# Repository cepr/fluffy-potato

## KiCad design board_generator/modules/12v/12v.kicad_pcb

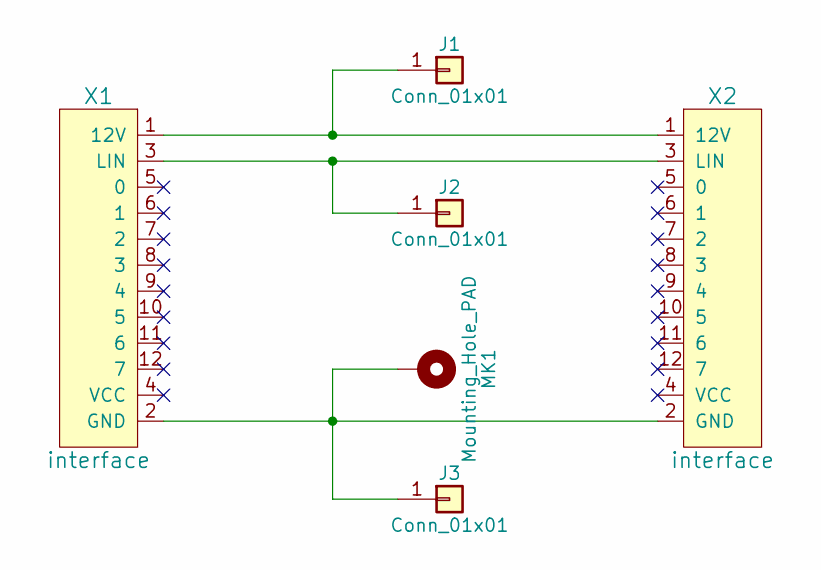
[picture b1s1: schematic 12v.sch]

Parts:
J1, J2, J3: Conn_01x01; SolderWirePad_single_SMD_5x10mm
MK1: Mounting_Hole_PAD; MountingHole_3.2mm_M3_Pad
X1, X2: interface

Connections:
unnamed: J1.1, X1.1 (12V), X2.1 (12V)
unnamed: J2.1, X1.3 (LIN), X2.3 (LIN)
unnamed: J3.1, MK1.1, X1.2 (GND), X2.2 (GND)

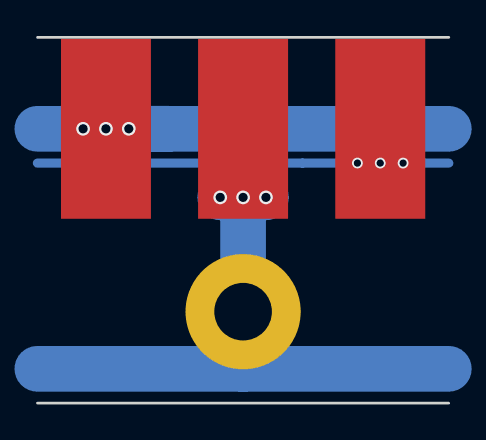
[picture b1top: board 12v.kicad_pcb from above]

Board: 2 copper layers, 22.9 x 20.3 mm, 6 parts (0 on the bottom side), 3 nets.

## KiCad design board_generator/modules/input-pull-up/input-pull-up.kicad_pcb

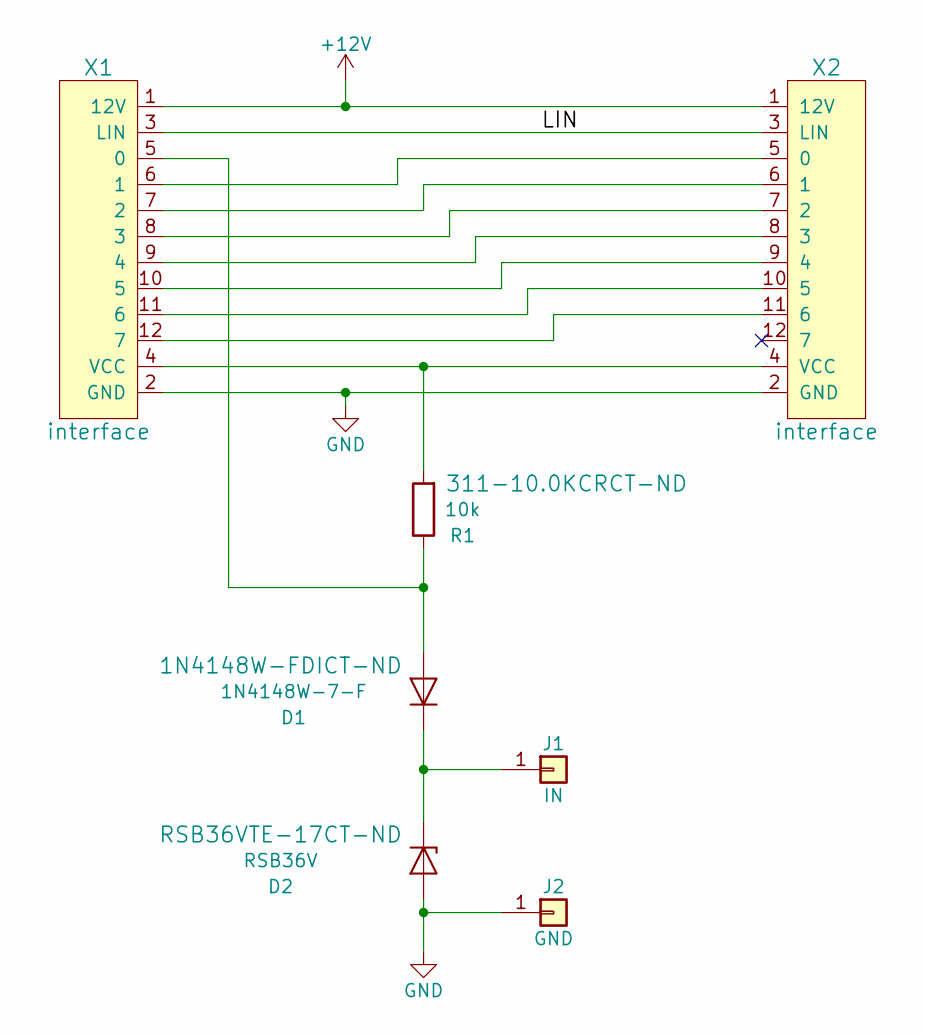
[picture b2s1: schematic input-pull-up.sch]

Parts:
D1: 1N4148W-7-F; D_SOD-123; DIGIKEY 1N4148W-FDICT-ND
D2: RSB36V; D_SOD-323; DIGIKEY RSB36VTE-17CT-ND
J1: IN; SolderWirePad_single_SMD_15x40mil
J2: GND; SolderWirePad_single_SMD_15x40mil
R1: 10k; R_0805; DIGIKEY 311-10.0KCRCT-ND
X1, X2: interface

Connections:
+12V: X1.1 (12V), X2.1 (12V)
/LIN: X1.3 (LIN), X2.3 (LIN)
GND: D2.2 (A), J2.1, X1.2 (GND), X2.2 (GND)
unnamed: D1.1 (K), D2.1 (K), J1.1
unnamed: D1.2 (A), R1.1, X1.5 (0)
unnamed: R1.2, X1.4 (VCC), X2.4 (VCC)
unnamed: X1.6 (1), X2.5 (0)
unnamed: X1.7 (2), X2.6 (1)
unnamed: X1.8 (3), X2.7 (2)
unnamed: X1.9 (4), X2.8 (3)
unnamed: X1.10 (5), X2.9 (4)
unnamed: X1.11 (6), X2.10 (5)
unnamed: X1.12 (7), X2.11 (6)

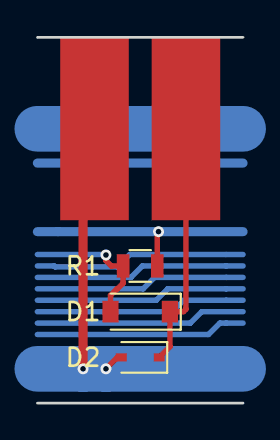
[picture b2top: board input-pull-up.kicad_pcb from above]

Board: 2 copper layers, 11.4 x 20.3 mm, 7 parts (0 on the bottom side), 13 nets.

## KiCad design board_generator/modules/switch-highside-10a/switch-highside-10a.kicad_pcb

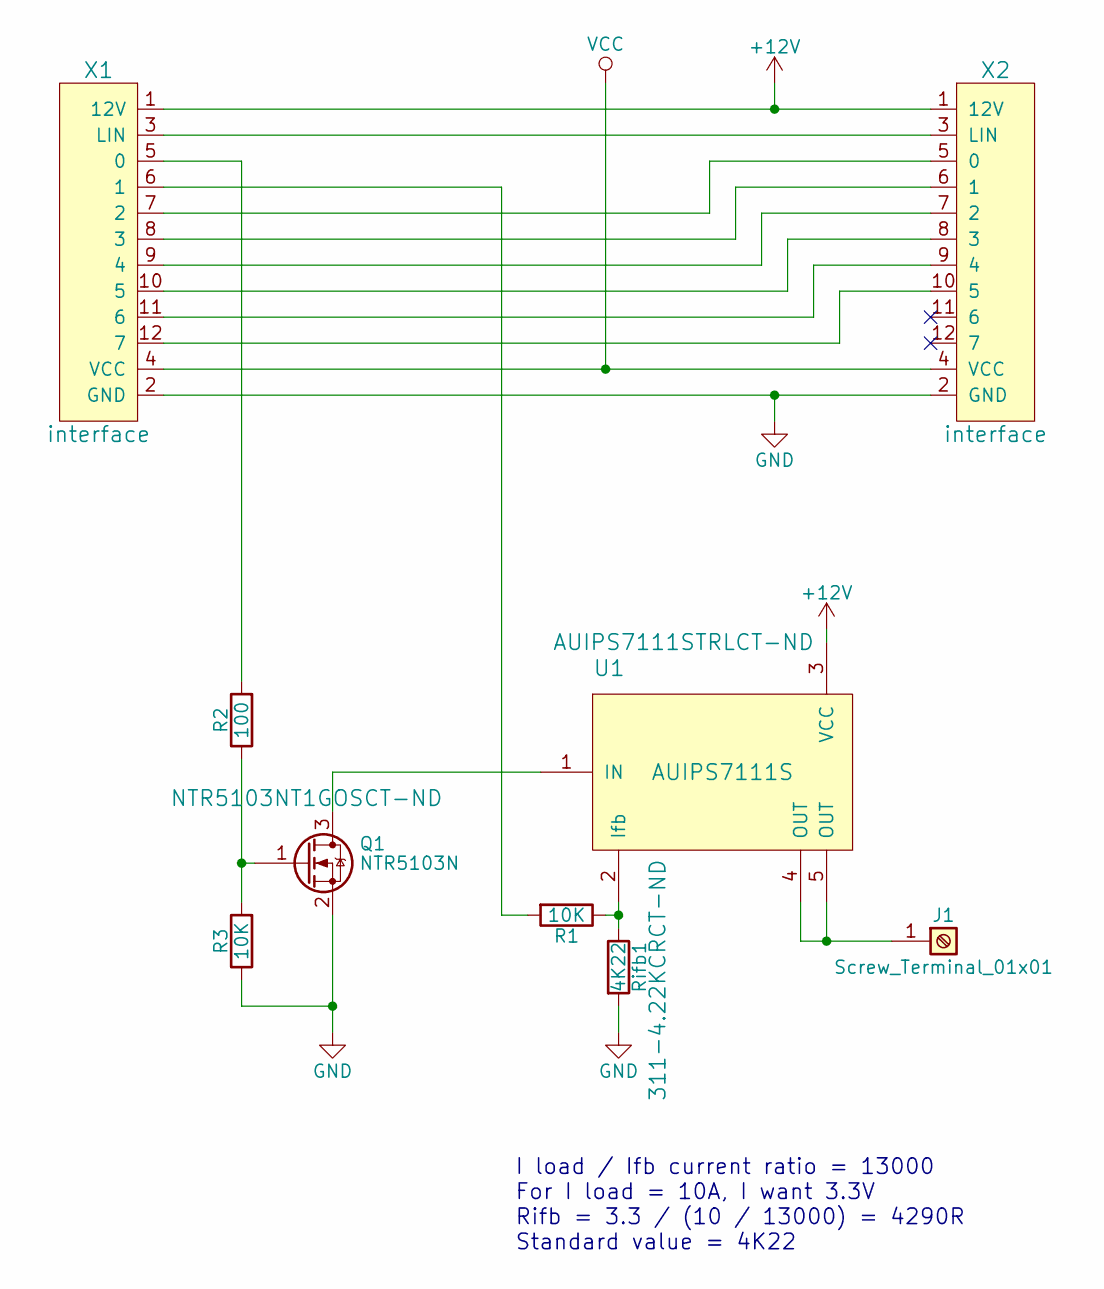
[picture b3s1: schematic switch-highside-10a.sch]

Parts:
J1: Screw_Terminal_01x01; TERM_SCREW_M3
Q1: NTR5103N; SOT-23; DIGIKEY NTR5103NT1GOSCT-ND
R1, R3: 10K; R_0805_HandSoldering; DIGIKEY 311-10.0KCRCT-ND
R2: 100; R_0805_HandSoldering; DIGIKEY 311-100CRCT-ND
Rifb1: 4K22; R_0805_HandSoldering; DIGIKEY 311-4.22KCRCT-ND
U1: AUIPS7111S; TO-263-5_TabPin3; DIGIKEY AUIPS7111STRLCT-ND
X1, X2: interface

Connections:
+12V: U1.3 (VCC), X1.1 (12V), X2.1 (12V)
GND: Q1.2 (S), R3.1, Rifb1.2, X1.2 (GND), X2.2 (GND)
unnamed: J1.1, U1.4 (OUT), U1.5 (OUT)
unnamed: Q1.1 (G), R2.1, R3.2
unnamed: Q1.3 (D), U1.1 (IN)
unnamed: R1.1, Rifb1.1, U1.2 (Ifb)
unnamed: R1.2, X1.6 (1)
unnamed: R2.2, X1.5 (0)
unnamed: X1.3 (LIN), X2.3 (LIN)
unnamed: X1.7 (2), X2.5 (0)
unnamed: X1.8 (3), X2.6 (1)
unnamed: X1.9 (4), X2.7 (2)
unnamed: X1.10 (5), X2.8 (3)
unnamed: X1.11 (6), X2.9 (4)
unnamed: X1.12 (7), X2.10 (5)
VCC: X1.4 (VCC), X2.4 (VCC)

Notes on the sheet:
I load / Ifb current ratio = 13000 For I load = 10A, I want 3.3V Rifb = 3.3 / (10 / 13000) = 4290R Standard value = 4K22

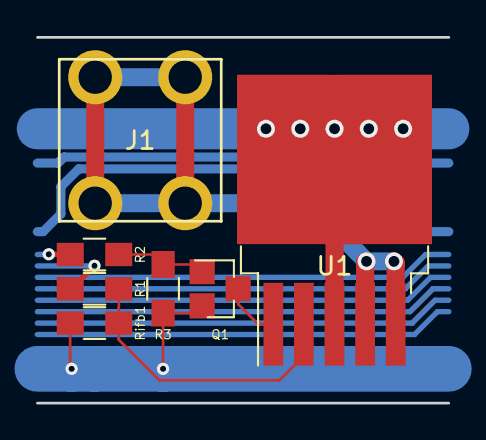
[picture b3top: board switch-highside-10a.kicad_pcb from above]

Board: 2 copper layers, 22.9 x 20.3 mm, 9 parts (0 on the bottom side), 16 nets.

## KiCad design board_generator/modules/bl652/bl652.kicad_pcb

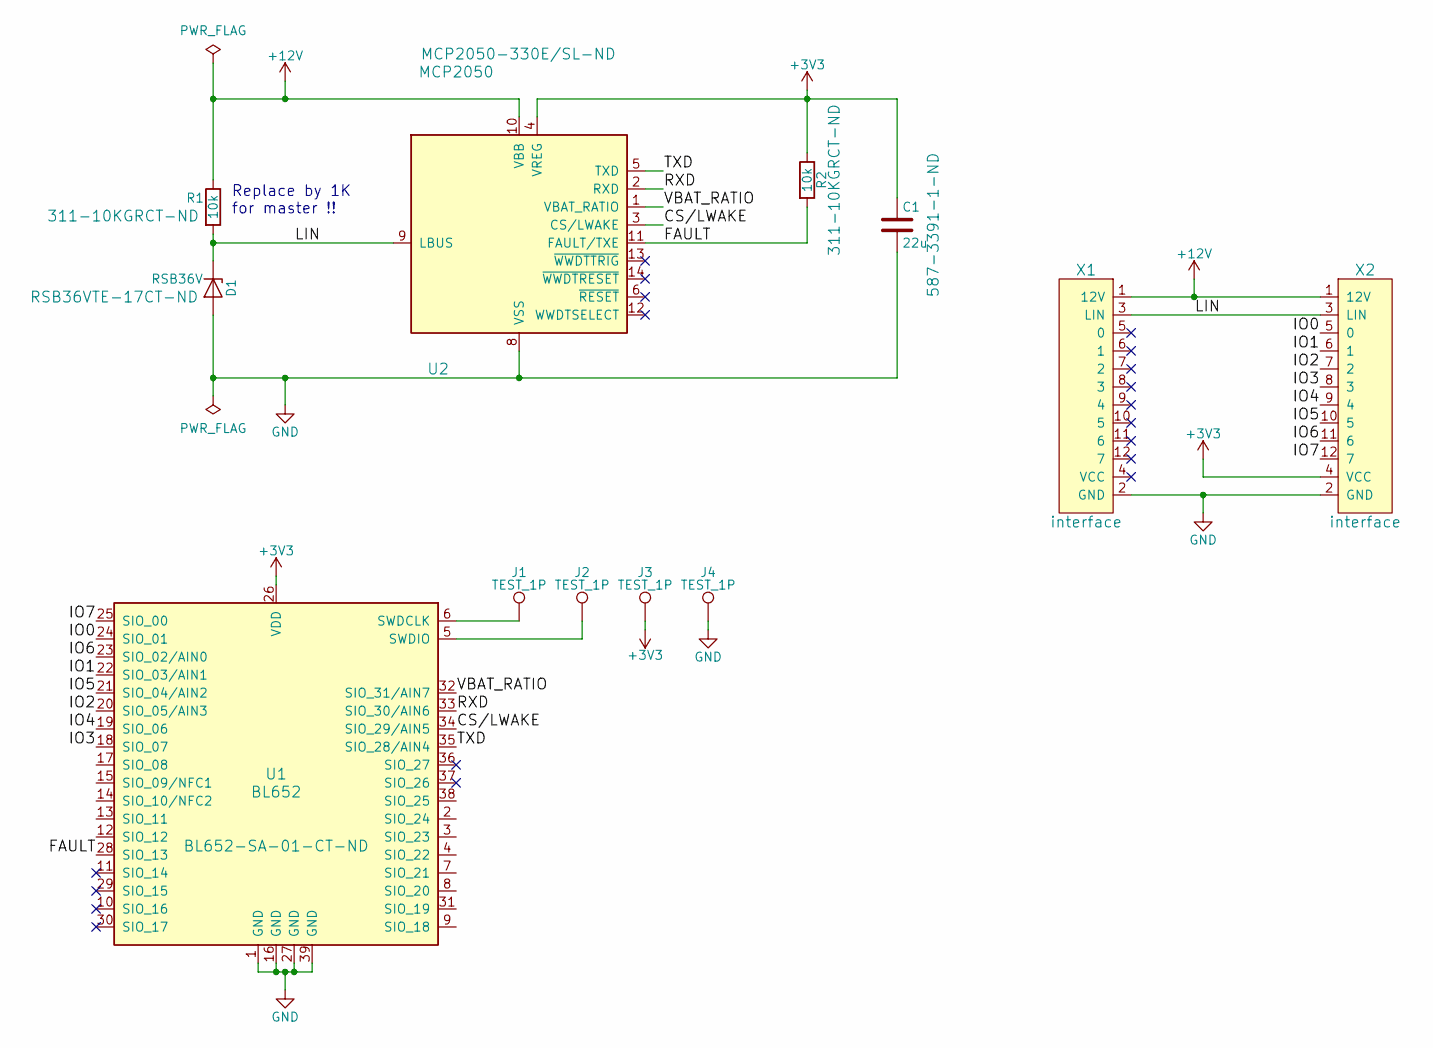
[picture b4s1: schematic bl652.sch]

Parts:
C1: 22u; C_0805_HandSoldering; DIGIKEY 587-3391-1-ND
D1: RSB36V; D_SOD-323_HandSoldering; DIGIKEY RSB36VTE-17CT-ND
J1, J2, J3, J4: TEST_1P; Measurement_Point_Square-SMD-Pad_Small
R1, R2: 10k; R_0603_HandSoldering; DIGIKEY 311-10KGRCT-ND
U1: BL652; Laird_BL652; DIGIKEY BL652-SA-01-CT-ND
U2: MCP2050; SOIC-14_3.9x8.7mm_Pitch1.27mm; DIGIKEY MCP2050-330E/SL-ND
X1, X2: interface

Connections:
+3V3: C1.1, J3.1, R2.1, U1.26 (VDD), U2.4 (VREG), X2.4 (VCC)
+12V: R1.1, U2.10 (VBB), X1.1 (12V), X2.1 (12V)
/CS/LWAKE: U1.34 (SIO_29/AIN5), U2.3 (CS/LWAKE)
/FAULT: R2.2, U1.28 (SIO_13), U2.11 (FAULT/TXE)
/IO0: U1.24 (SIO_01), X2.5 (0)
/IO1: U1.22 (SIO_03/AIN1), X2.6 (1)
/IO2: U1.20 (SIO_05/AIN3), X2.7 (2)
/IO3: U1.18 (SIO_07), X2.8 (3)
/IO4: U1.19 (SIO_06), X2.9 (4)
/IO5: U1.21 (SIO_04/AIN2), X2.10 (5)
/IO6: U1.23 (SIO_02/AIN0), X2.11 (6)
/IO7: U1.25 (SIO_00), X2.12 (7)
/LIN: D1.1 (K), R1.2, U2.9 (LBUS), X1.3 (LIN), X2.3 (LIN)
/RXD: U1.33 (SIO_30/AIN6), U2.2 (RXD)
/TXD: U1.35 (SIO_28/AIN4), U2.5 (TXD)
/VBAT_RATIO: U1.32 (SIO_31/AIN7), U2.1 (VBAT_RATIO)
GND: C1.2, D1.2 (A), J4.1, U1.1 (GND), U1.16 (GND), U1.27 (GND), U1.39 (GND), U2.8 (VSS), X1.2 (GND), X2.2 (GND)
unnamed: J1.1, U1.6 (SWDCLK)
unnamed: J2.1, U1.5 (SWDIO)

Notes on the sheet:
Replace by 1K for master !!

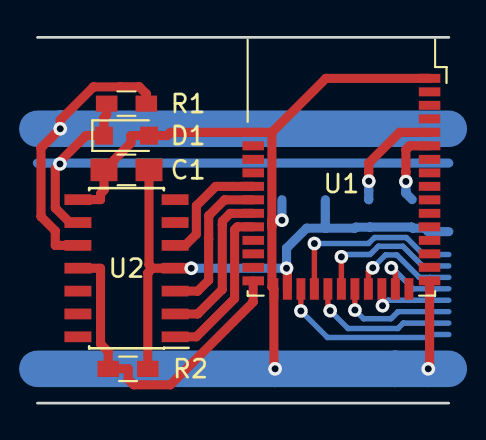
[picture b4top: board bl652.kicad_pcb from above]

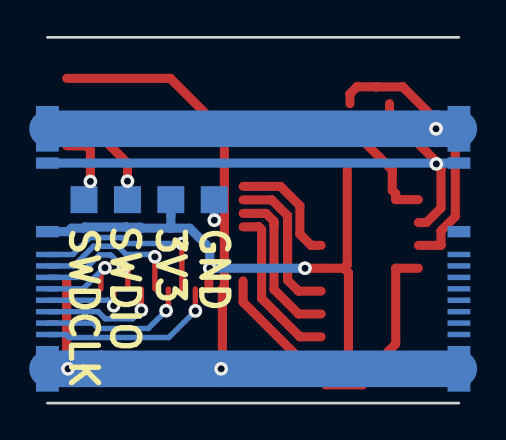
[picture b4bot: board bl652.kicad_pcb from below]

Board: 2 copper layers, 22.9 x 20.3 mm, 12 parts (4 on the bottom side), 19 nets.

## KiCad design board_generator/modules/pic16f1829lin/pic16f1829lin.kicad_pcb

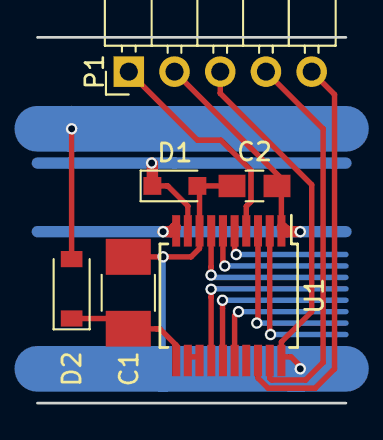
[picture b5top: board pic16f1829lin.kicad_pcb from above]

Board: 2 copper layers, 17.1 x 20.3 mm, 8 parts (0 on the bottom side), 17 nets.

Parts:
C1: 10uF; C_1210_HandSoldering
C2: 1uF; C_0805_HandSoldering
D1: RSB36V; D_SOD-323_HandSoldering
D2: 1N4148W-7-F; D_SOD-123
P1: MOLEX-22-28-6050; Pin_Header_Angled_1x05_Pitch2.54mm
U1: PIC16F1829LIN; SSOP-20_5.3x7.2mm_Pitch0.65mm
X1, X2: interface

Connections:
+5V: C2.1, P1.2, U1.1, U1.10, X1.4, X2.4
+12V: D2.2, X1.1, X2.1
//MCLR: P1.1, U1.4
/ICSPCLK: P1.5, U1.18
/ICSPDAT: P1.4, U1.19
/LBUS: D1.1, U1.9, X1.3, X2.3
/RA4: U1.3, X2.11
/RA5: U1.2, X2.12
/RC0: U1.16, X2.10
/RC1: U1.15, X2.9
/RC2: U1.14, X2.8
/RC3: U1.7, X2.7
/RC4: U1.6, X2.6
/RC5: U1.5, X2.5
GND: C1.2, C2.2, D1.2, P1.3, U1.8, U1.20, X1.2, X2.2
unnamed: C1.1, D2.1, U1.11
unnamed: U1.12, U1.13

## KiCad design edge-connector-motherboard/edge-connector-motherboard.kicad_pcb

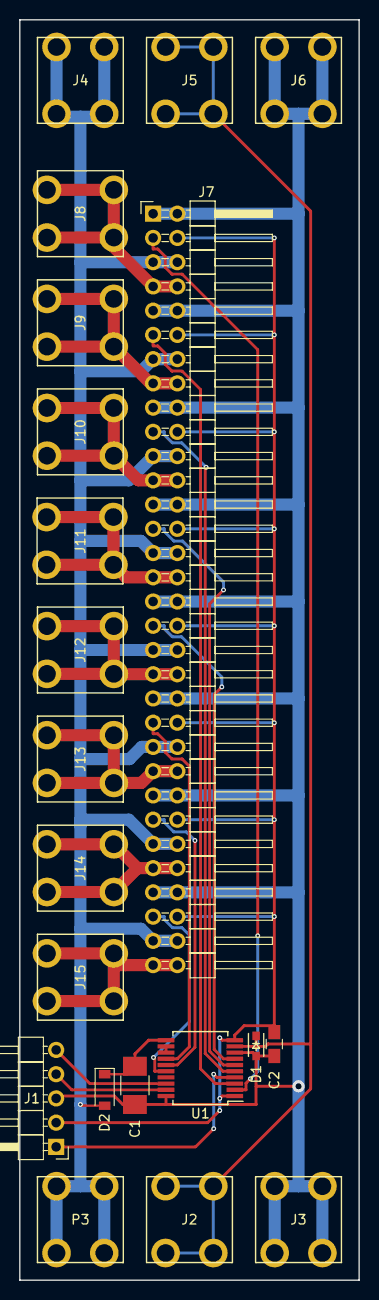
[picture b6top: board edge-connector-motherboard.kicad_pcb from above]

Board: 2 copper layers, 35.6 x 132.1 mm, 21 parts (0 on the bottom side), 26 nets.

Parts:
C1: 10uF; C_1210_HandSoldering
C2: 1uF; C_0805_HandSoldering
D1: RSB36V; SOD-323_HandSoldering
D2: 1N4148W-7-F; D_SOD-123
J1, J2, J3, J4, J5, J6, J8, J9, J10, J11, J12, J13, J14, J15: Screw_Terminal_1x01; TERM_SCREW_M3
J7: CONN_02X32; Pin_Header_Angled_2x32_Pitch2.54mm
P3: MOLEX-22-28-6050; Pin_Header_Angled_1x05_Pitch2.54mm
U1: PIC16F1829LIN; SSOP-20_5.3x7.2mm_Pitch0.65mm

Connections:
+5V: C2.1, J7.4, J7.12, J7.20, J7.28, J7.36, J7.44, J7.52, J7.60, P3.2, U1.1, U1.10
+12V: D2.2, J1.1, J4.1, J7.5, J7.6, J7.13, J7.14, J7.21, J7.22, J7.29, J7.30, J7.37, J7.38, J7.45, J7.46, J7.53, J7.54, J7.61, J7.62
/D1: J7.3, U1.2
/D2: J7.11, U1.3
/D3: J7.19, U1.5
/D4: J7.27, U1.6
/D5: J7.35, U1.7
/D6: J7.43, U1.14
/D7: J7.51, U1.15
/D8: J7.59, U1.16
/E1: J7.7, J7.8, J8.1
/E2: J7.15, J7.16, J9.1
/E3: J7.23, J7.24, J10.1
/E4: J7.31, J7.32, J11.1
/E5: J7.39, J7.40, J12.1
/E6: J7.47, J7.48, J13.1
/E7: J7.55, J7.56, J14.1
/E8: J7.63, J7.64, J15.1
/PIC16F1829LIN//MCLR: P3.1, U1.4
/PIC16F1829LIN/ICSPCLK: P3.5, U1.18
/PIC16F1829LIN/ICSPDAT: P3.4, U1.19
/PIC16F1829LIN/LBUS: D1.1, J2.1, J5.1, U1.9
GND: C1.2, C2.2, D1.2, P3.3, U1.8, U1.20
GNDPWR: J3.1, J6.1, J7.1, J7.2, J7.9, J7.10, J7.17, J7.18, J7.25, J7.26, J7.33, J7.34, J7.41, J7.42, J7.49, J7.50, J7.57, J7.58
unnamed: C1.1, D2.1, U1.11
unnamed: U1.12, U1.13

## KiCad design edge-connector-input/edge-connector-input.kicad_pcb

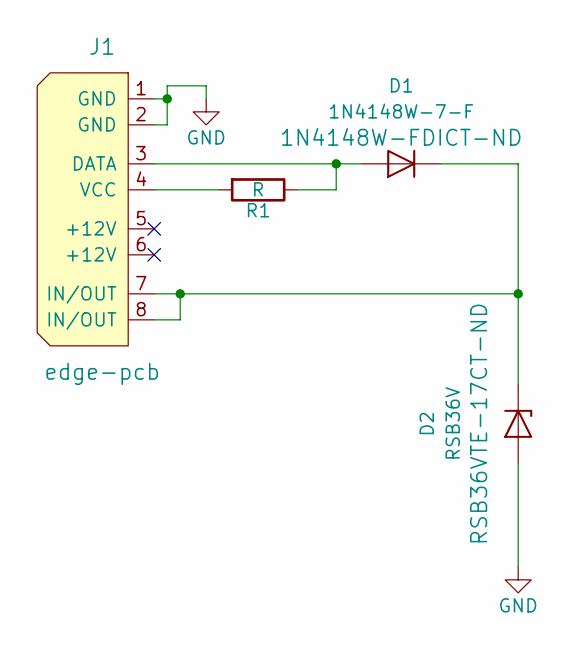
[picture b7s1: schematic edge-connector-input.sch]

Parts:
D1: 1N4148W-7-F; D_SOD-123; DIGIKEY 1N4148W-FDICT-ND
D2: RSB36V; D_SOD-323; DIGIKEY RSB36VTE-17CT-ND
J1: edge-pcb
R1: R; R_0805

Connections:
GND: D2.2 (A), J1.1 (GND), J1.2 (GND)
unnamed: D1.1 (K), D2.1 (K), J1.7 (IN/OUT), J1.8 (IN/OUT)
unnamed: D1.2 (A), J1.3 (DATA), R1.1
unnamed: J1.4 (VCC), R1.2

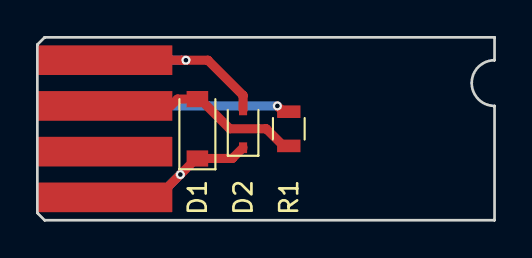
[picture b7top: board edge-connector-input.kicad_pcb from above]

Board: 2 copper layers, 25.4 x 10.2 mm, 4 parts (0 on the bottom side), 4 nets.

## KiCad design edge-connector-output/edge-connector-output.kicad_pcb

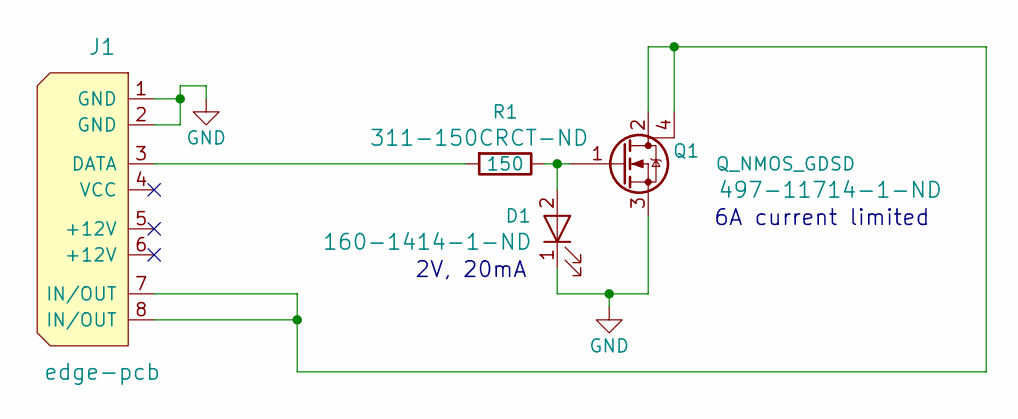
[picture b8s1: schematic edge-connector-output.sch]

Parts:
D1: LITEON-LTST-C170KGKT; LED_0805; DIGIKEY 160-1414-1-ND
J1: edge-pcb
Q1: Q_NMOS_GDSD; SOT-223; DIGIKEY 497-11714-1-ND
R1: 150; R_0805; DIGIKEY 311-150CRCT-ND

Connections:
GND: D1.1 (K), J1.1 (GND), J1.2 (GND), Q1.3 (S)
unnamed: D1.2 (A), Q1.1 (G), R1.1
unnamed: J1.3 (DATA), R1.2
unnamed: J1.7 (IN/OUT), J1.8 (IN/OUT), Q1.2 (D), Q1.4 (D)

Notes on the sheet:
2V, 20mA
6A current limited

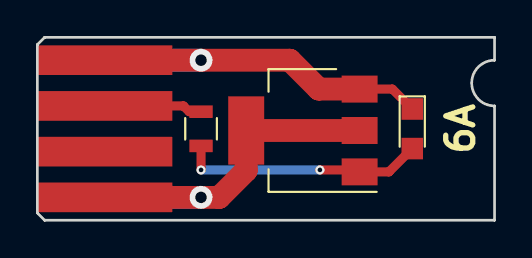
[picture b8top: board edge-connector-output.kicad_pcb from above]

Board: 2 copper layers, 25.4 x 10.2 mm, 4 parts (0 on the bottom side), 4 nets.

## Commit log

2016-10-03 First working firmware
2016-10-12 4x13A switch - rev 1
2016-10-12 9 inputs LIN module - rev1
2016-10-16 Activating sleep mode - down to 180uA without LIN communication
2016-10-27 inputs rev1, 13a_switch_x4 rev1
    both hardware and firmware is working
2016-12-01 lin_bluetooth_gateway rev2
2016-12-04 13a_switch rev2
    - daisy-chain connector
    - adding a DIP switch to select the LIN device
2016-12-11 minor updates (DigiKey PN, cleaning)
2016-12-12 8 inputs rev 2
2016-12-20 [bluetooth module] Swapping R1 and D1 references on layout
2016-12-27 Updating microchip code
2016-12-27 Adding nRF5 SDK for lin_bluetooth_gateway
2016-12-27 Refactoring directories
2016-12-27 Using RF_Modules instead of Bluetooth_Modules for BL652
2016-12-27 Moving MCP2050 symbol to "microchip" library
2016-12-27 Moving PIC16F1829LIN symbol to microchip library
2016-12-27 Using SW_DIP_x04 from KiCad library
2017-01-02 Using BL652 from rfcomm library
2017-01-02 [13a_switch_x4] Using official libraries
2017-01-02 [13a_switch_x4] Lock mounting holes
2017-01-02 [inputs] Updating to use standard libraries
2017-02-20 Updating build tools
2017-02-21 First working NRF52 master with two slave PIC nodes
    # Software
    * Using LIN 2.x checksum instead of LIN 1.x
    * Using 19200 baudrate instead of 20000 for compatibility with NRF52
    * Setting only the NRF52 as master
    * Deactivating sleep mode for PIC as it was broken
    * Ignoring break signal (not generated by NRF52 yet)
2017-07-03 edge-connector-motherboard
2017-07-03 Updating sub-modules
2017-07-04 edge-connector-output
2017-07-04 edge-connector-input
2017-07-04 edge-connector-motherboard: adding 3d models and digikey references
2017-08-01 board_generator
2017-08-01 first test of the edgeconnector motherboards
2017-08-04 board_generator work in progress
2017-08-04 board_generator: support for drill and edge cut layers
2017-08-12 work in progress
2017-09-05 Adding BL652 module
2017-09-05 bl652 and edge complete
2017-10-25 Adding comodo, front_lights and rear_lights module
2017-10-25 Adding input (12v and lin) connectors - ordered!
2017-12-29 Adding engine board
2018-01-10 Adding CircleCI configuration
2018-01-10 Updating compiler version in Makefile
2018-01-10 Generating Makefiles during build process
2018-01-10 fixed config file
2018-01-10 Adding compilation rules for board_generator
2018-01-10 Fixing compilation issue in board_generator
2018-01-10 Adding qtcreator project files for inputs/src
2018-01-12 [board_generator] Fixing compilation
2018-01-16 Adding switch high-side 10a
2018-01-17 Adding pull-down on switch-highside-10a to disable output by default
2018-01-17 fab engine rev1
2018-01-21 Using custom Docker image for the build
2018-01-23 Refactor of the PIC firmware
2018-01-23 Fixing CircleCI build
2018-01-23 Adding missing Makefiles
2018-01-23 steering_wheel firmware implementation
2018-01-23 front_light (left and right) implementation
2018-01-23 horn implementation
2018-01-23 Implementing engine
2018-03-20 Adding value and DigiKey reference for R1 on input-pull-up
2018-03-20 Adding DigiKey references for switch-highside-10a
2018-03-20 Adding PIC to horn, windshield and rear_window_defogger
2018-03-29 Updating firmware
2018-03-29 adding BOM
2018-04-08 engine_rev2, windshield_rev2: adding WIPERS_REST_POSITION and fixing analog
2018-04-08 Working firmware for front_lights, rear_lights, horn,
2018-11-05 Using solder pads for 12v module
2018-11-05 steering_wheel board with solder pads
2018-11-05 Using solder pads for module input_pull_up
